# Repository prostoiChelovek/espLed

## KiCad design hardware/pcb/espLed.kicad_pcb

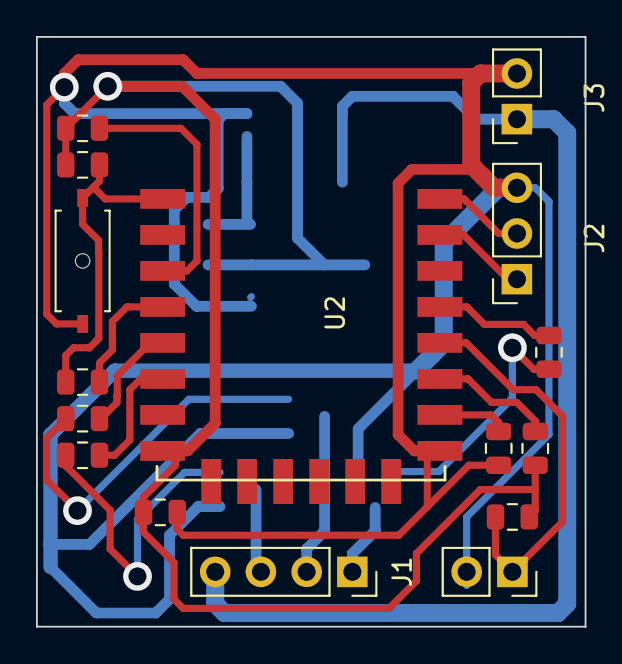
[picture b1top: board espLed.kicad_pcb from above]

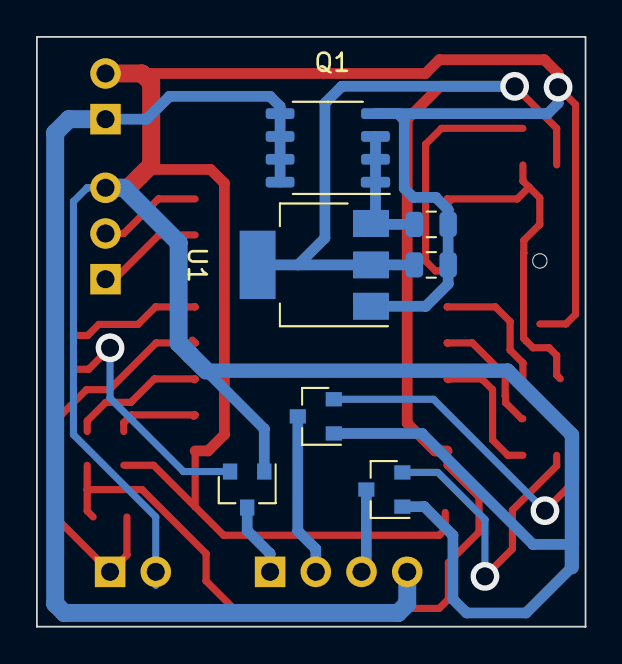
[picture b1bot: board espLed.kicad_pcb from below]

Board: 2 copper layers, 30.5 x 32.8 mm, 23 parts (7 on the bottom side), 21 nets.

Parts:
C1: 10uF; C_0805_2012Metric
C2: 22uF; C_0805_2012Metric
C3: 100uF; C_0805_2012Metric
J1: led_strip; PinSocket_1x04_P2.54mm_Vertical
J2: flashing; PinSocket_1x03_P2.54mm_Vertical
J3: power; PinSocket_1x02_P2.54mm_Vertical
Q1: IRF9310TRPBF; IRF9310PBF
Q2, Q3, Q4: AO3400A; AO3400
R1, R2, R3: 220; R_0805_2012Metric
R4, R6, R7, R8, R9: 10k; R_0805_2012Metric
R5: 470; R_0805_2012Metric
SW1: reset; push_button
SW2: flash; PinSocket_1x02_P2.54mm_Vertical
U1: AMS1117-3.3; SOT-223-3_TabPin2
U2: ESP-12F; ESP-12E_SMD

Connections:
+3V3: C2.1, C3.1, R4.1, R6.1, R7.1, R8.1, U1.2, U2.8
+12V: C1.1, Q1.3, U1.3
/12v_in: J1.4, J3.1, Q1.1
/RX: J2.2, U2.16
/TX: J2.1, U2.15
/led1: R3.2, U2.13
/led1_out: J1.1, Q2.1
/led2: R1.2, U2.5
/led2_out: J1.2, Q3.1
/led3: R2.2, U2.6
/led3_out: J1.3, Q4.1
GND: C1.2, C2.2, C3.2, J2.3, J3.2, Q1.2, Q2.3, Q3.3, Q4.3, R9.1, SW1.1, SW2.2, U1.1, U2.9
unnamed: Q2.2, R3.1
unnamed: Q3.2, R1.1
unnamed: Q4.2, R2.1
unnamed: R4.2, R5.2, SW1.2, U2.1
unnamed: R5.1, U2.4
unnamed: R6.2, U2.3
unnamed: R7.2, SW2.1, U2.12
unnamed: R8.2, U2.11
unnamed: R9.2, U2.10

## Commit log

2021-01-10 move kicad files to a subdirectory
2021-01-10 add a library for esp8266
2021-01-10 layout a schematic for the power regulator
2021-01-10 add a reverse input voltage protection
2021-01-10 layout a basic circuitry for esp-12f
2021-01-10 add labels for used pins and add connector for flashing
2021-01-10 layout mosfets and add a connector for the led strip
2021-01-10 layout schematic into block so it looks nice
2021-01-10 assign pcb footprints to the rest of components and annotate schematic
    except for the reset button
2021-01-10 create a footprint for button and assign it to reset
2021-01-10 fix default SO-8 footprint for IRF9310TRPBF mosfet
2021-01-10 fix default SOT23 footprint for AO3400 mosfet
2021-01-10 layout the power part of the circuit
2021-01-10 layout circuitry for ESP
2021-01-10 layout the 'led driver' part of the scheme
2021-01-10 move the reset button and rearrange some components around it
2021-01-10 move the 'flash' jumper to save a bit of space
2021-01-10 rearrange vias on the left side to save a bit of space
2021-01-10 arrange components on the right side tighter
2021-01-10 place power part into it's position and connect some of the power pins
2021-01-10 replace GND with 12V in led strip connector
2021-01-10 connect GNDs of two transistors and make strip's 12v trace thicker
2021-01-10 connect GND of the remaining transistor and make 12V traces thicker
2021-01-10 connect 3v3 of the regulator to ESP and connect GND of the "reset" btn
2021-01-10 add a board outline and show dimensions
2021-01-11 move power circuitry upwards and make traces power nearby thicker
2021-01-11 make power connections to ESP thicker
2021-01-11 disconnect GND of two transistors, move decoupling capacitor to bottom
2021-01-11 rewire two transistors' GNDs neater
2021-01-11 reroute GND of the 'flash' jumper to fit leds' 12v tighter
2021-01-11 fix the board outline
2021-01-11 fix ESP's 3d model and move led connector to the top layer (just visual)
2021-01-13 move components on the left side downwards to save space
2021-01-13 move power vias to the left and reconnect everything
2021-01-13 connect forgotten wire and fix board outline
